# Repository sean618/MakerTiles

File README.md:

# MakerTiles

MakerTiles is a system of modular, snap-together electronic tiles. Each tile is a
small STM32-based board with a single job — a strip of LEDs, a joystick, a motor,
a distance sensor, a screen, a speaker, and so on. Tiles connect on a shared bus,
a USB tile bridges the bus to a PC, and a Python daemon on the PC discovers every
connected tile and lets you read its inputs and drive its outputs.

This repository holds the whole stack: the **hardware** (KiCad board designs), the
**firmware** (STM32 board projects + shared driver libraries), the **protocols**
that move data over the bus, and the **daemon** that talks to it all from a PC.

```
    [ tile ]──[ tile ]──[ tile ]── … ──[ USB tile ]──USB──▶ [ PC / Python daemon ]
       └───────────────────────────────────┘
          shared SPI bus  (MicroBus + Field Protocol)
```

## How it fits together

Two protocols stacked on top of each other carry everything:

- **MicroBus** — the transport. A master/multi-node protocol over a shared
  SPI-style link between microcontrollers, built for speed and very low RAM:
  fixed-size packets, a time-slotted schedule the master broadcasts in every
  packet, and a small per-node sliding window that gives reliable, in-order
  delivery with no dynamic allocation.
- **Field Protocol** — the application layer. Rides inside a MicroBus packet and
  describes each tile as a set of named, typed **fields** (e.g. a LED strip's
  colour, a dial's position). The daemon enumerates tiles, reads their field
  tables, and gets/sets field values without knowing the tile type in advance.

One tile acts as the **master** (the USB tile, which also bridges the bus to a
host PC). Every other tile is a **node**. On the PC, the daemon opens the USB
serial port, discovers the attached tiles, and exposes each one as an object you
can interact with.

## Repository layout

```
hardware/        KiCad designs for every tile (Boards/) + shared symbol/footprint
                 libraries, 3D models and BOMs (Libraries/). Old/ holds retired
                 prototype boards.

firmware/        STM32 firmware.
  Boards/          One STM32CubeIDE project per tile (Button, LedStrip, Motor,
                   Joystick, Screen, USB, …). Mostly STM32G030 nodes; the USB
                   master is an STM32F103.
  Libraries/       Shared C/C++ drivers used across boards (ledStrip, screen,
                   imu, speaker, servos, …) plus helpers (myAssert, fonts).
  Documents/       NewBoardSetup.txt — the checklist for bringing up a new tile
                   (CubeMX peripheral config + firmware wiring).

protocol/        The shared protocol code, host-buildable and testable.
  microbus/        MicroBus transport (C++). Leaf component.
  fieldprotocol/   Field Protocol (C++), depends on microbus. Also built as the
                   masterNodeSystem shared library the Python daemon loads.
  stm32/           STM32 glue binding the protocols to real SPI hardware
                   (stm32F1SpiMaster, stm32Node). Boards reach this via a
                   Core/stm32 symlink.

daemon/          Python daemon (the PC side). Opens the USB serial port, runs
                   board discovery, and drives tiles over the Field Protocol.
                   src/makertiles/ is the package; tests/ holds its test suites.

tests/system/    Full C stack (node + master) over the real MicroBus, in-process.

tools/           Helper scripts (e.g. logparser.py).
```

## The PC daemon

The daemon is a Python package (`makertiles`, src-layout under `daemon/`). At a
high level you point it at a serial port and it hands you back the discovered
tiles:

```python
import makertiles

tiles, manager = makertiles.start(port_name="/dev/ttyUSB0")

tiles.led_strip.colour = makertiles.red   # set an output field
position = tiles.dial.position             # read an input field
```

It can drive the C protocol two ways: over **serial** to real hardware in
production, or — in tests — by loading the `masterNodeSystem` shared library
directly via `ctypes`, so the real Python daemon exercises the real C protocol
without any hardware attached. That same library is what catches drift between
the C and Python sides of the wire contract.

Optional extras: `Pillow` (`images`) for the screen image-drawing helpers.

## Building and testing

The C components and the Python daemon build in one CMake tree, and every test
suite runs from a single command:

```bash
./build_and_test.sh
```

This configures, builds (MicroBus, the Field Protocol + its shared library, and
the system test), then runs `ctest`. Python test deps (`pytest`, `pyserial`) are
installed automatically if missing.

To re-run only the failures, verbosely:

```bash
ctest --test-dir build --rerun-failed --output-on-failure
```

### Test suites

| CTest name           | What it covers                                              |
|----------------------|-------------------------------------------------------------|
| `microbus_unit`      | MicroBus transport unit tests (host).                       |
| `fieldprotocol_unit` | Field Protocol unit tests against a mock MicroBus.          |
| `system_integration` | Full C stack (node + master) over the real MicroBus.        |
| `python_unit`        | Python Field-Protocol encode/decode round trips.            |
| `python_integration` | The real Python daemon driving the C protocol via the .so.  |

`python_integration` is the suite that exercises both languages together, so it
is the one that catches C↔Python wire-contract drift.

The firmware board projects under `firmware/Boards/` are separate
STM32CubeIDE/CMake projects and are **not** part of the host build above — they
are flashed to real tiles. See `firmware/Documents/NewBoardSetup.txt` for the
per-board hardware and firmware bring-up checklist.

## Building firmware for a tile

Each `firmware/Boards/<Tile>/` directory is its own STM32 project (`.ioc` for
CubeMX, a linker script for the target part, and CubeIDE debug launch configs).
Nodes are generally STM32G030; the USB master is an STM32F103. The protocol
sources are shared into each board via symlinks (`Core/stm32`,
`Core/Libraries`, etc.) rather than copied — see the setup checklist for the
exact links and the required SPI/timer/interrupt peripheral configuration.

## License

Released under the [MIT License](LICENSE).

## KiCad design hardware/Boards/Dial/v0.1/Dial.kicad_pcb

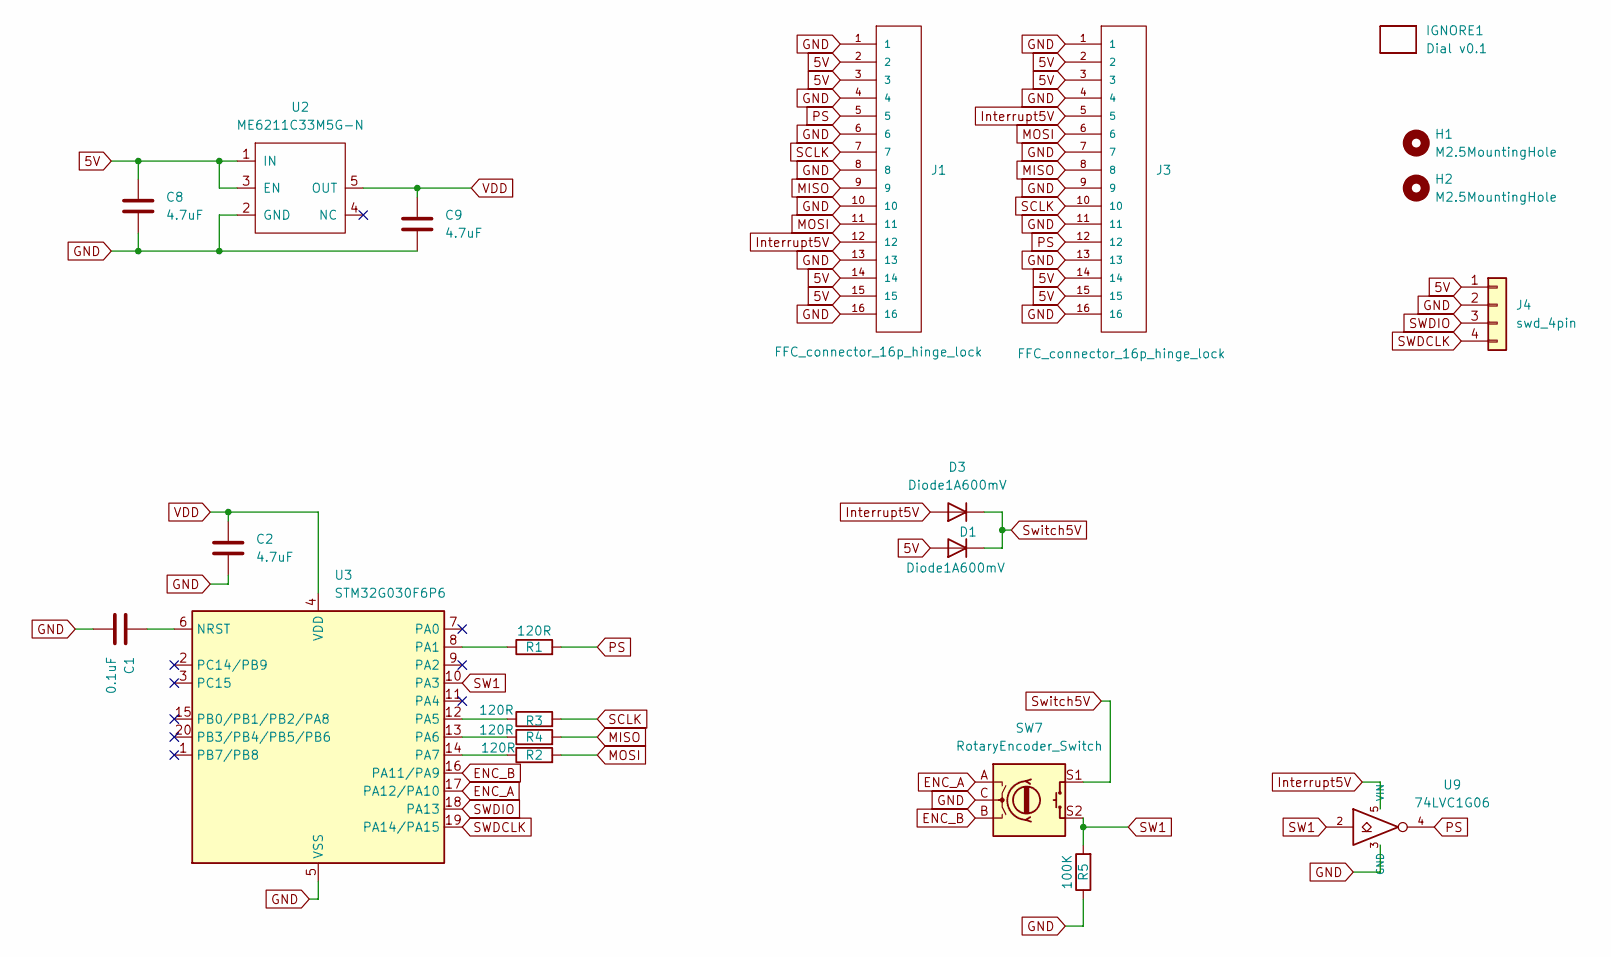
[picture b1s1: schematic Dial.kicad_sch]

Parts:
C1: 0.1uF; C_0402_1005Metric
C2, C8, C9: 4.7uF; C_0402_1005Metric
D1, D3: Diode1A600mV; D_SOD-323
H1, H2: M2.5MountingHole; MountingHole_2.7mm_M2.5_ISO7380
IGNORE1: Dial v0.1; BoardText
J1, J3: FFC_connector_16p_hinge_lock
J4: swd_4pin; swd_header
R1, R2, R3, R4: 120R; R_0402_1005Metric
R5: 100K; R_0402_1005Metric
SW7: RotaryEncoder_Switch; RotaryEncoderEC12D
U2: ME6211C33M5G-N; SOT-23-5
U3: STM32G030F6P6; TSSOP-20_4.4x6.5mm_P0.65mm
U9: 74LVC1G06; SOT-353_SC-70-5

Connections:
5V: C8.1, D1.2 (A), J1.2, J1.3, J1.14, J1.15, J3.2, J3.3, J3.14, J3.15, J4.1, U2.1 (IN), U2.3 (EN)
ENC_A: SW7.A, U3.17 (PA12/PA10)
ENC_B: SW7.B, U3.16 (PA11/PA9)
GND: C1.2, C2.2, C8.2, C9.2, J1.1, J1.4, J1.6, J1.8, J1.10, J1.13, J1.16, J3.1, J3.4, J3.7, J3.9, J3.11, J3.13, J3.16, J4.2, R5.1, SW7.C, U2.2 (GND), U3.5 (VSS), U9.3 (GND)
Interrupt5V: D3.2 (A), J1.12, J3.5, U9.5 (VIN)
MISO: J1.9, J3.8, R4.2
MOSI: J1.11, J3.6, R2.2
unnamed: C1.1, U3.6 (NRST)
unnamed: R1.1, U3.8 (PA1)
unnamed: R3.1, U3.12 (PA5)
unnamed: R4.1, U3.13 (PA6)
unnamed: R2.1, U3.14 (PA7)
PS: J1.5, J3.12, R1.2, U9.4
SCLK: J1.7, J3.10, R3.2
SW1: R5.2, SW7.S2, U3.10 (PA3), U9.2
SWDCLK: J4.4, U3.19 (PA14/PA15)
SWDIO: J4.3, U3.18 (PA13)
Switch5V: D1.1 (K), D3.1 (K), SW7.S1
VDD: C2.1, C9.1, U2.5 (OUT), U3.4 (VDD)

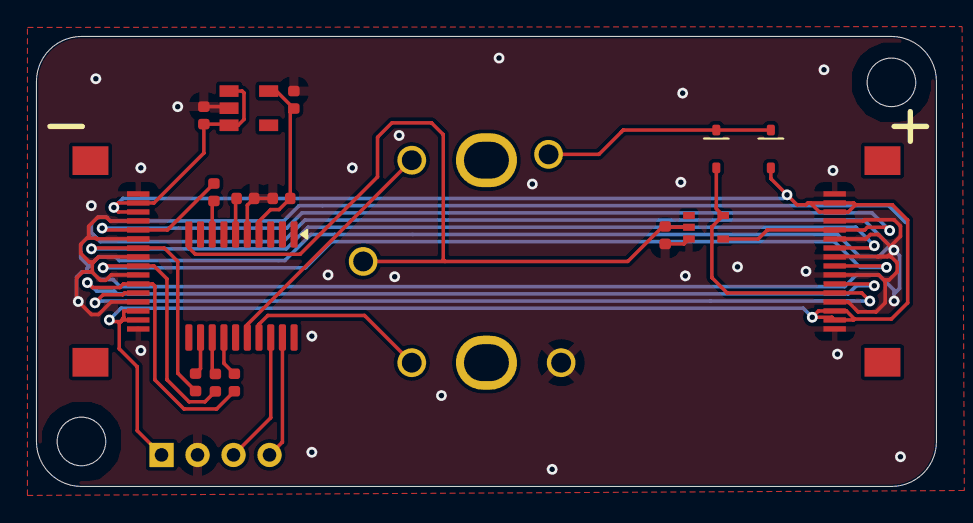
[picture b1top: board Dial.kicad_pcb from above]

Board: 2 copper layers, 50.0 x 25.0 mm, 21 parts (0 on the bottom side), 19 nets.

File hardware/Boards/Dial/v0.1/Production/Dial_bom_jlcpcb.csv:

Comment,Designator,Footprint,LCSC Part Number
4.7uF,"C9,C8,C2",C_0402_1005Metric,C23733
FFC_connector_16p_hinge_lock,"J1,J3",FFC_connector_16p_hinge_lock,C262665
Diode1A600mV,"D3,D1",D_SOD-323,C191023
74LVC1G06,U9,SOT-353_SC-70-5,C460519
ME6211C33M5G-N,U2,SOT-23-5,C81233
120R,"R2,R4,R1,R3",R_0402_1005Metric,C25079
RotaryEncoder_Switch,SW7,RotaryEncoderEC12D,C112349
STM32G030F6P6,U3,TSSOP-20_4.4x6.5mm_P0.65mm,C529330
100K,R5,R_0402_1005Metric,C25741
0.1uF,C1,C_0402_1005Metric,C1525

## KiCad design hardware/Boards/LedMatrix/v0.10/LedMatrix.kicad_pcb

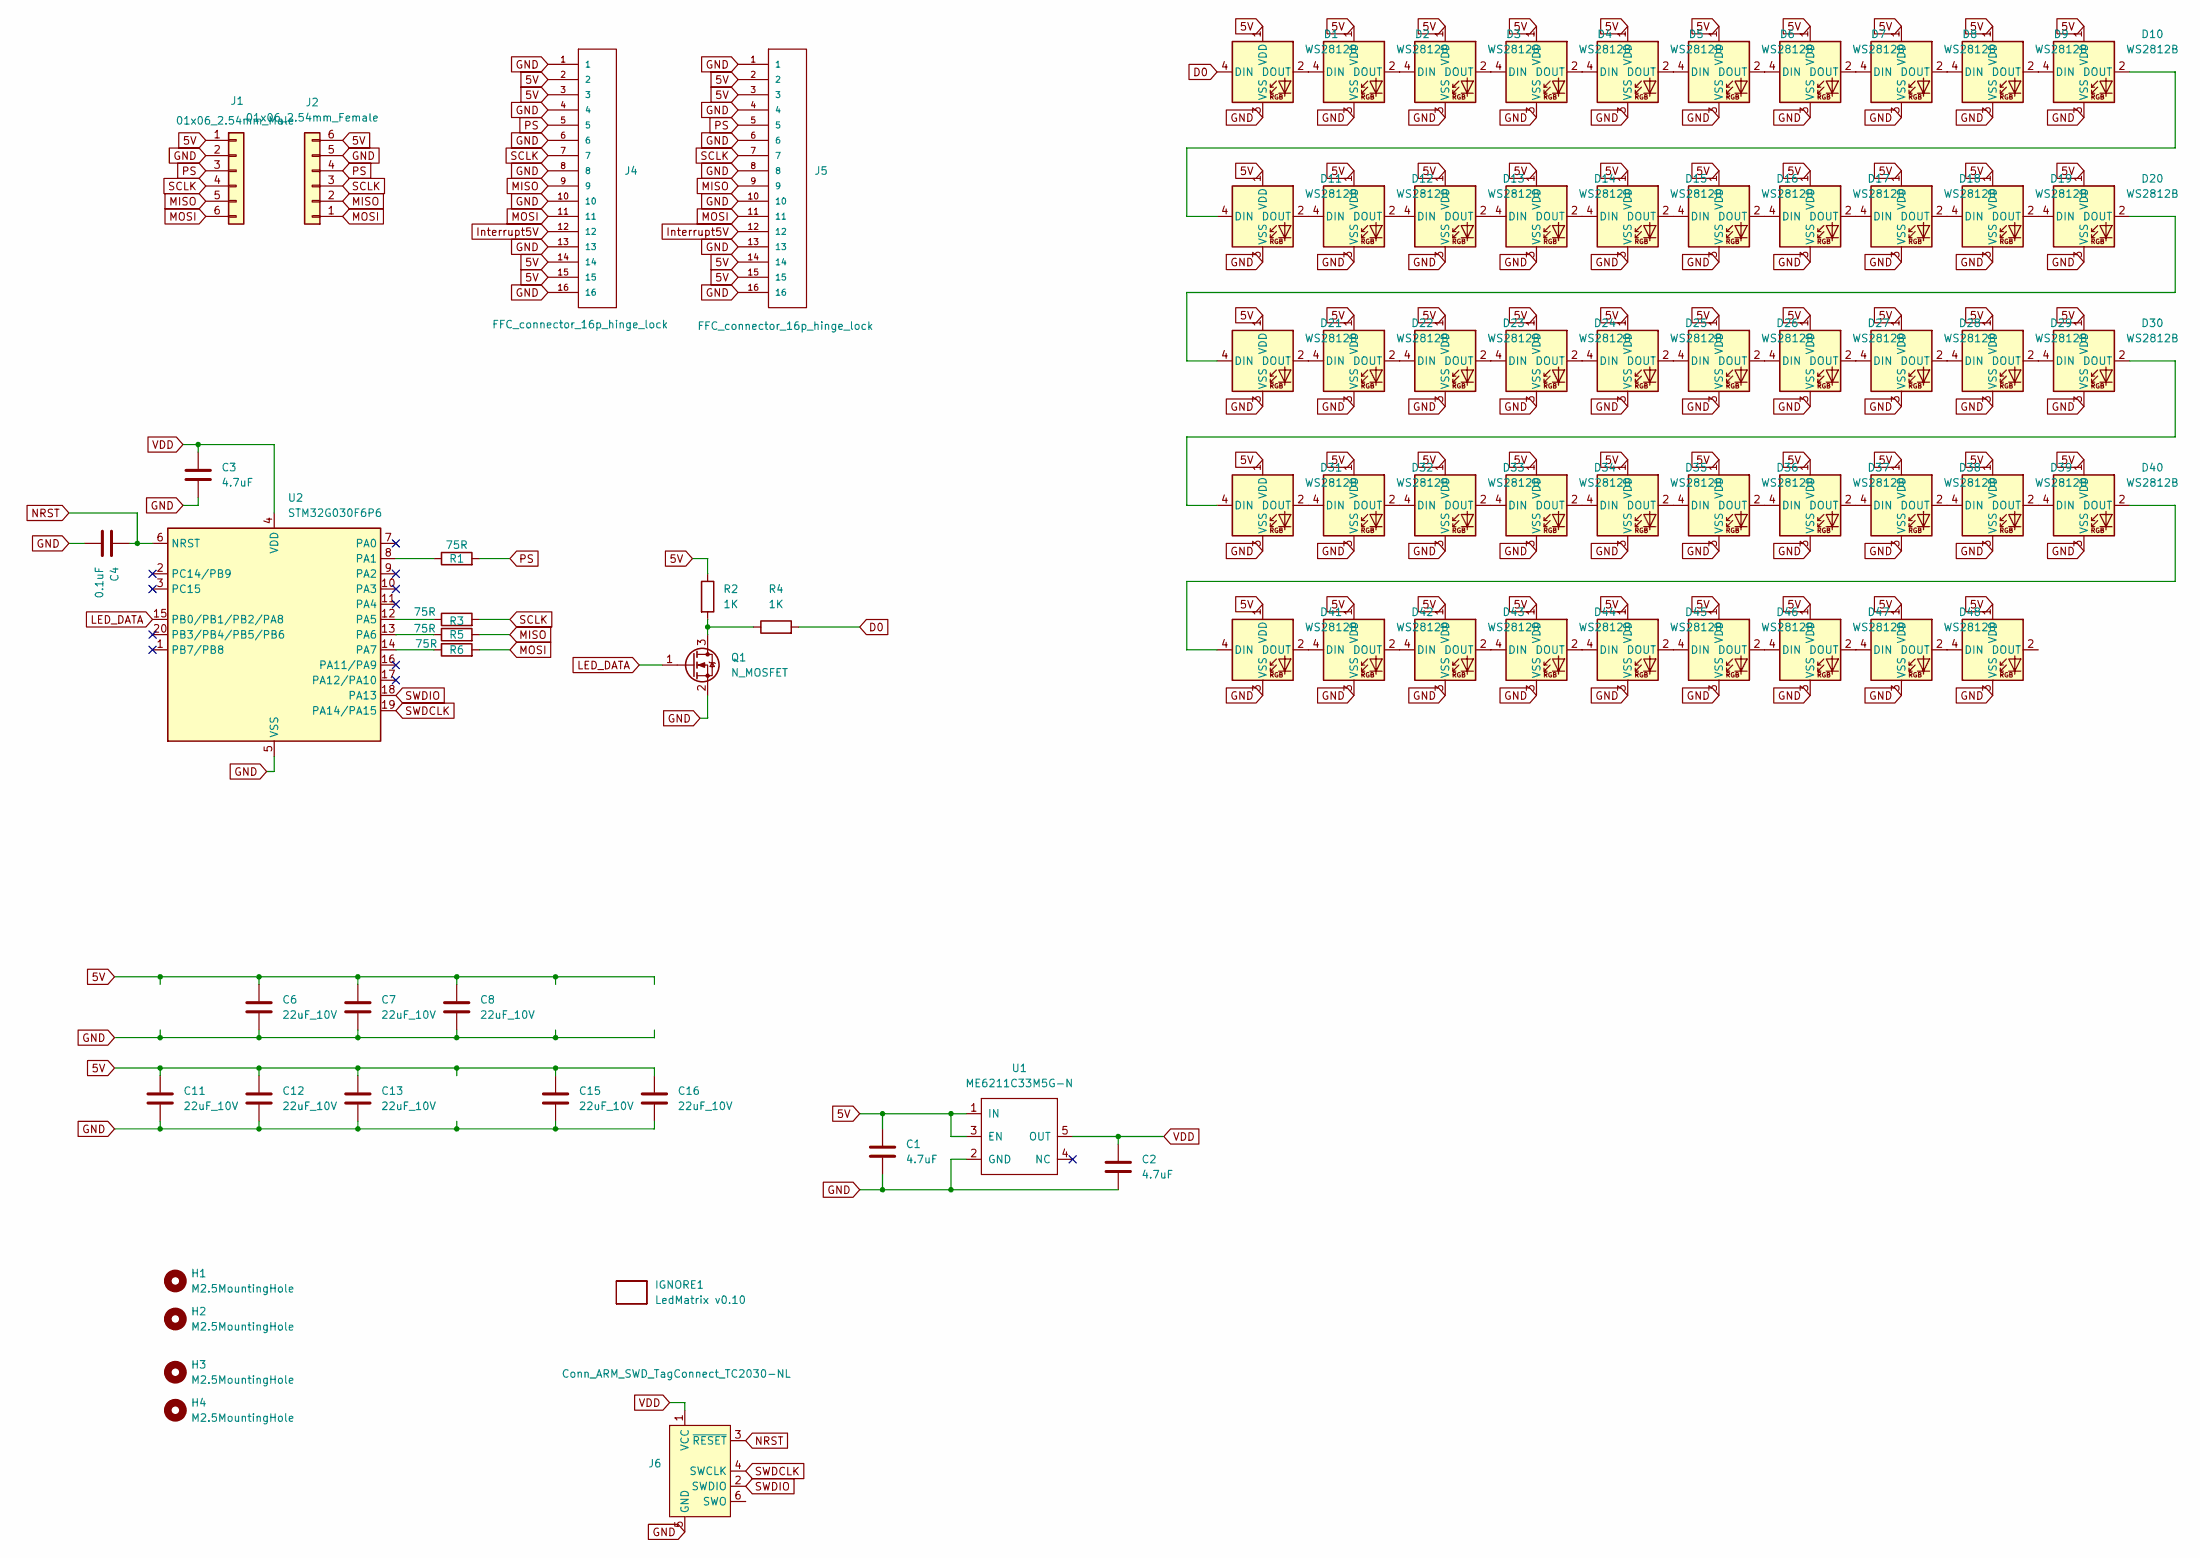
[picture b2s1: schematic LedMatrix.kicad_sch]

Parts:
C1, C2, C3: 4.7uF; C_0402_1005Metric
C4: 0.1uF; C_0402_1005Metric
C6, C7, C8, C11, C12, C13, C15, C16: 22uF_10V; C_0603_1608Metric
D1, D2, D3, D4, D5, D6, D7, D8, D9, D10, D11, D12, D13, D14, D15, D16, D17, D18, D19, D20, D21, D22, D23, D24, D25, D26, D27, D28, D29, D30, D31, D32, D33, D34, D35, D36, D37, D38, D39, D40, D41, D42, D43, D44, D45, D46, D47, D48, D49: WS2812B; LED_WS2812B_PLCC4_5.0x5.0mm_P3.2mm
H1, H2, H3, H4: M2.5MountingHole; MountingHole_2.7mm_M2.5_ISO7380
IGNORE1: LedMatrix v0.10; BoardText
J1: 01x06_2.54mm_Male
J2: 01x06_2.54mm_Female
J4, J5: FFC_connector_16p_hinge_lock
J6: Conn_ARM_SWD_TagConnect_TC2030-NL; Tag-Connect_TC2030-IDC-NL_2x03_P1.27mm_Vertical
Q1: N_MOSFET; SOT-23
R1, R3, R5, R6: 75R; R_0402_1005Metric
R2, R4: 1K; R_0402_1005Metric
U1: ME6211C33M5G-N; SOT-23-5
U2: STM32G030F6P6; TSSOP-20_4.4x6.5mm_P0.65mm

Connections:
5V: C1.1, C6.1, C7.1, C8.1, C11.1, C12.1, C13.1, C15.1, C16.1, D1.1 (VDD), D2.1 (VDD), D3.1 (VDD), D4.1 (VDD), D5.1 (VDD), D6.1 (VDD), D7.1 (VDD), D8.1 (VDD), D9.1 (VDD), D10.1 (VDD), D11.1 (VDD), D12.1 (VDD), D13.1 (VDD), D14.1 (VDD), D15.1 (VDD), D16.1 (VDD), D17.1 (VDD), D18.1 (VDD), D19.1 (VDD), D20.1 (VDD), D21.1 (VDD), D22.1 (VDD), D23.1 (VDD), D24.1 (VDD), D25.1 (VDD), D26.1 (VDD), D27.1 (VDD), D28.1 (VDD), D29.1 (VDD), D30.1 (VDD), D31.1 (VDD), D32.1 (VDD), D33.1 (VDD), D34.1 (VDD), D35.1 (VDD), D36.1 (VDD), D37.1 (VDD), D38.1 (VDD), D39.1 (VDD), D40.1 (VDD), D41.1 (VDD), D42.1 (VDD), D43.1 (VDD), D44.1 (VDD), D45.1 (VDD), D46.1 (VDD), D47.1 (VDD), D48.1 (VDD), D49.1 (VDD), J1.1, J2.6, J4.2, J4.3, J4.14, J4.15, J5.2, J5.3, J5.14, J5.15, R2.1, U1.1 (IN), U1.3 (EN)
D0: D1.4 (DIN), R4.2
GND: C1.2, C2.2, C3.2, C4.2, C6.2, C7.2, C8.2, C11.2, C12.2, C13.2, C15.2, C16.2, D1.3 (VSS), D2.3 (VSS), D3.3 (VSS), D4.3 (VSS), D5.3 (VSS), D6.3 (VSS), D7.3 (VSS), D8.3 (VSS), D9.3 (VSS), D10.3 (VSS), D11.3 (VSS), D12.3 (VSS), D13.3 (VSS), D14.3 (VSS), D15.3 (VSS), D16.3 (VSS), D17.3 (VSS), D18.3 (VSS), D19.3 (VSS), D20.3 (VSS), D21.3 (VSS), D22.3 (VSS), D23.3 (VSS), D24.3 (VSS), D25.3 (VSS), D26.3 (VSS), D27.3 (VSS), D28.3 (VSS), D29.3 (VSS), D30.3 (VSS), D31.3 (VSS), D32.3 (VSS), D33.3 (VSS), D34.3 (VSS), D35.3 (VSS), D36.3 (VSS), D37.3 (VSS), D38.3 (VSS), D39.3 (VSS), D40.3 (VSS), D41.3 (VSS), D42.3 (VSS), D43.3 (VSS), D44.3 (VSS), D45.3 (VSS), D46.3 (VSS), D47.3 (VSS), D48.3 (VSS), D49.3 (VSS), J1.2, J2.5, J4.1, J4.4, J4.6, J4.8, J4.10, J4.13, J4.16, J5.1, J5.4, J5.6, J5.8, J5.10, J5.13, J5.16, J6.5 (GND), Q1.2 (S), U1.2 (GND), U2.5 (VSS)
Interrupt5V: J4.12, J5.12
LED_DATA: Q1.1 (G), U2.15 (PB0/PB1/PB2/PA8)
MISO: J1.5, J2.2, J4.9, J5.9, R5.2
MOSI: J1.6, J2.1, J4.11, J5.11, R6.2
NRST: C4.1, J6.3 (~RESET), U2.6 (NRST)
unnamed: D1.2 (DOUT), D2.4 (DIN)
unnamed: D2.2 (DOUT), D3.4 (DIN)
unnamed: D3.2 (DOUT), D4.4 (DIN)
unnamed: D4.2 (DOUT), D5.4 (DIN)
unnamed: D5.2 (DOUT), D6.4 (DIN)
unnamed: D6.2 (DOUT), D7.4 (DIN)
unnamed: D7.2 (DOUT), D8.4 (DIN)
unnamed: D8.2 (DOUT), D9.4 (DIN)
unnamed: D9.2 (DOUT), D10.4 (DIN)
unnamed: D10.2 (DOUT), D11.4 (DIN)
unnamed: D11.2 (DOUT), D12.4 (DIN)
unnamed: D12.2 (DOUT), D13.4 (DIN)
unnamed: D13.2 (DOUT), D14.4 (DIN)
unnamed: D14.2 (DOUT), D15.4 (DIN)
unnamed: D15.2 (DOUT), D16.4 (DIN)
unnamed: D16.2 (DOUT), D17.4 (DIN)
unnamed: D17.2 (DOUT), D18.4 (DIN)
unnamed: D18.2 (DOUT), D19.4 (DIN)
unnamed: D19.2 (DOUT), D20.4 (DIN)
unnamed: D20.2 (DOUT), D21.4 (DIN)
unnamed: D21.2 (DOUT), D22.4 (DIN)
unnamed: D22.2 (DOUT), D23.4 (DIN)
unnamed: D23.2 (DOUT), D24.4 (DIN)
unnamed: D24.2 (DOUT), D25.4 (DIN)
unnamed: D25.2 (DOUT), D26.4 (DIN)
unnamed: D26.2 (DOUT), D27.4 (DIN)
unnamed: D27.2 (DOUT), D28.4 (DIN)
unnamed: D28.2 (DOUT), D29.4 (DIN)
unnamed: D29.2 (DOUT), D30.4 (DIN)
unnamed: D30.2 (DOUT), D31.4 (DIN)
unnamed: D31.2 (DOUT), D32.4 (DIN)
unnamed: D32.2 (DOUT), D33.4 (DIN)
unnamed: D33.2 (DOUT), D34.4 (DIN)
unnamed: D34.2 (DOUT), D35.4 (DIN)
unnamed: D35.2 (DOUT), D36.4 (DIN)
unnamed: D36.2 (DOUT), D37.4 (DIN)
unnamed: D37.2 (DOUT), D38.4 (DIN)
unnamed: D38.2 (DOUT), D39.4 (DIN)
unnamed: D39.2 (DOUT), D40.4 (DIN)
unnamed: D40.2 (DOUT), D41.4 (DIN)
unnamed: D41.2 (DOUT), D42.4 (DIN)
unnamed: D42.2 (DOUT), D43.4 (DIN)
unnamed: D43.2 (DOUT), D44.4 (DIN)
unnamed: D44.2 (DOUT), D45.4 (DIN)
unnamed: D45.2 (DOUT), D46.4 (DIN)
unnamed: D46.2 (DOUT), D47.4 (DIN)
unnamed: D47.2 (DOUT), D48.4 (DIN)
unnamed: D48.2 (DOUT), D49.4 (DIN)
unnamed: Q1.3 (D), R2.2, R4.1
unnamed: R1.1, U2.8 (PA1)
unnamed: R3.1, U2.12 (PA5)
unnamed: R5.1, U2.13 (PA6)
unnamed: R6.1, U2.14 (PA7)
PS: J1.3, J2.4, J4.5, J5.5, R1.2
SCLK: J1.4, J2.3, J4.7, J5.7, R3.2
SWDCLK: J6.4 (SWCLK), U2.19 (PA14/PA15)
SWDIO: J6.2 (SWDIO), U2.18 (PA13)
VDD: C2.1, C3.1, J6.1 (VCC), U1.5 (OUT), U2.4 (VDD)

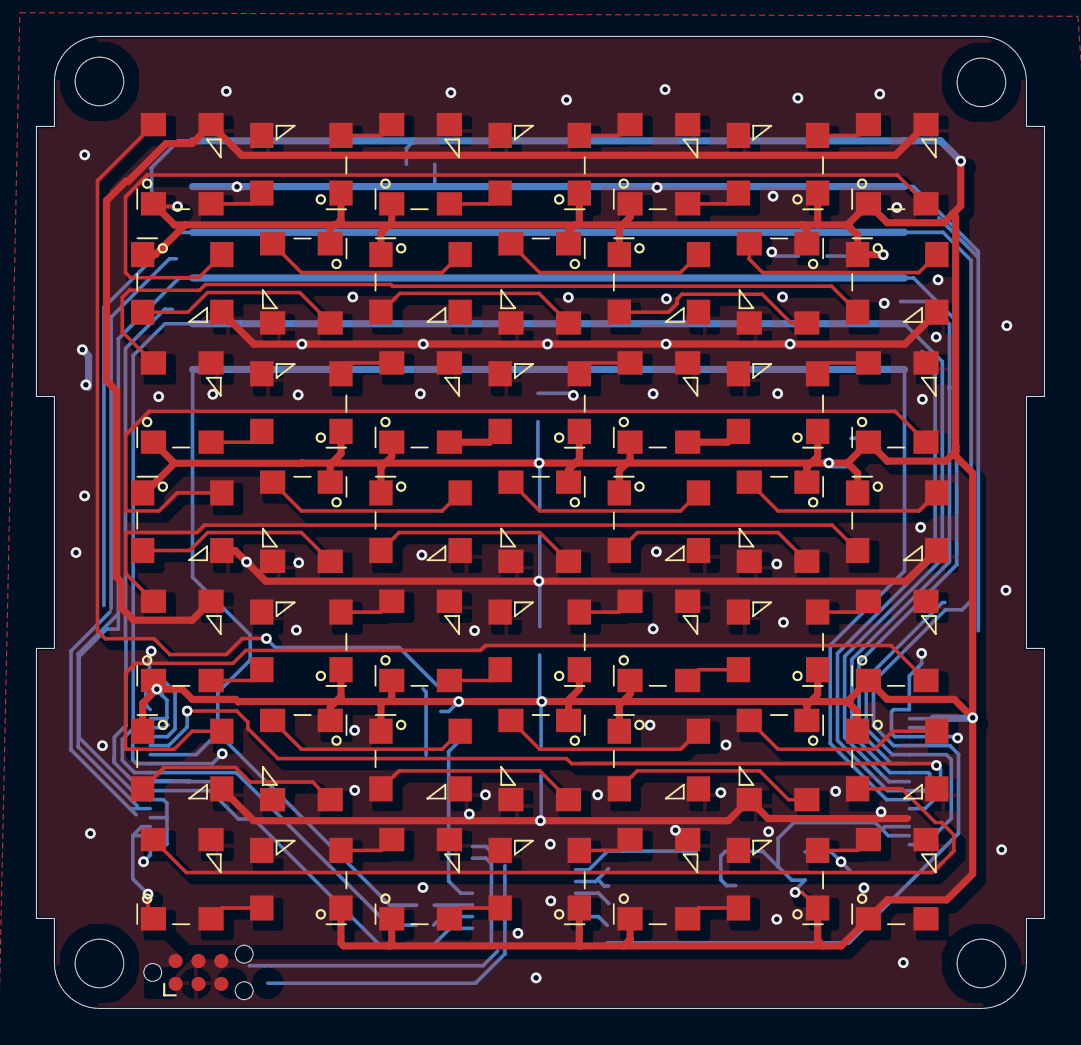
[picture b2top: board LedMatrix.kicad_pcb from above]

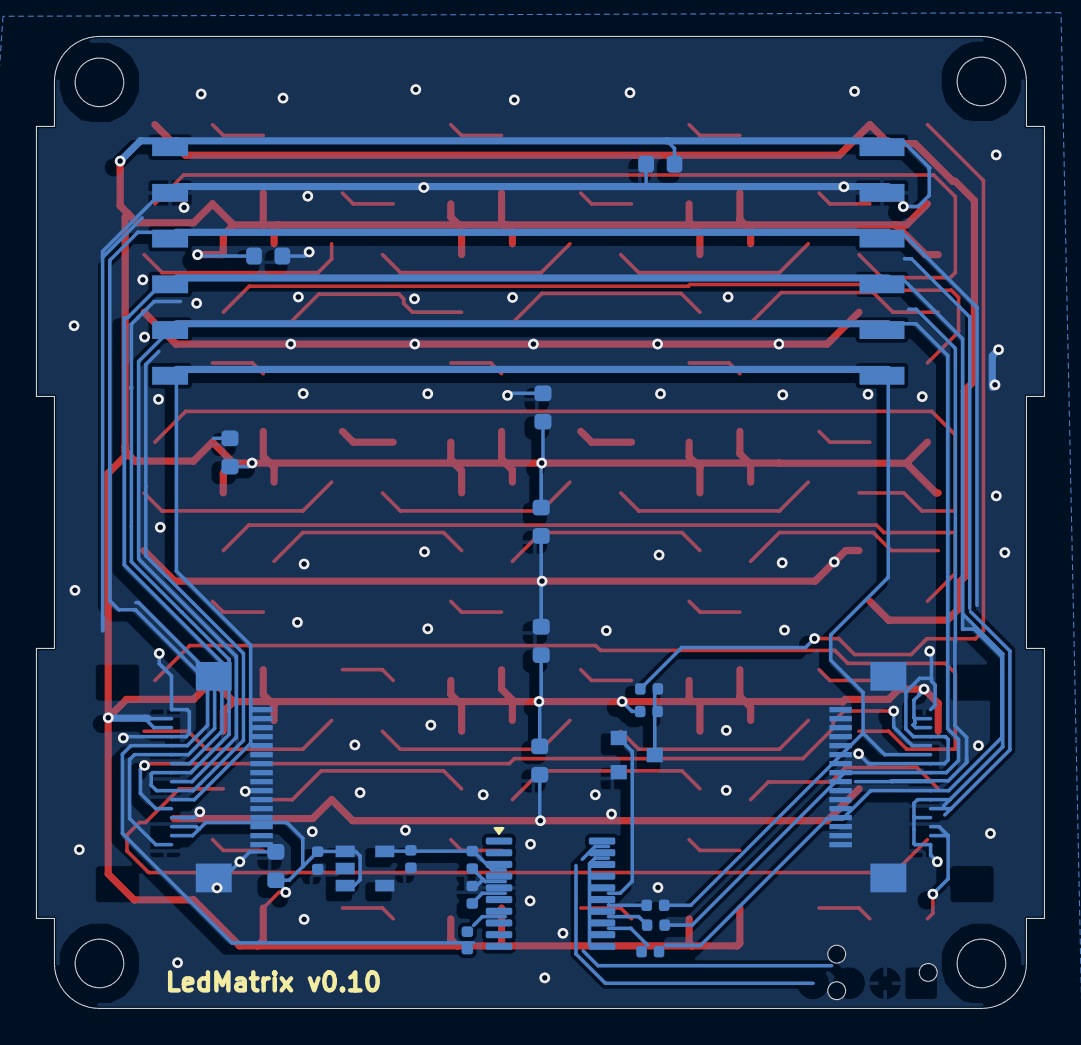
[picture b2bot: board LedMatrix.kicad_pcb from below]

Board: 4 copper layers, 56.0 x 54.0 mm, 80 parts (25 on the bottom side), 66 nets.

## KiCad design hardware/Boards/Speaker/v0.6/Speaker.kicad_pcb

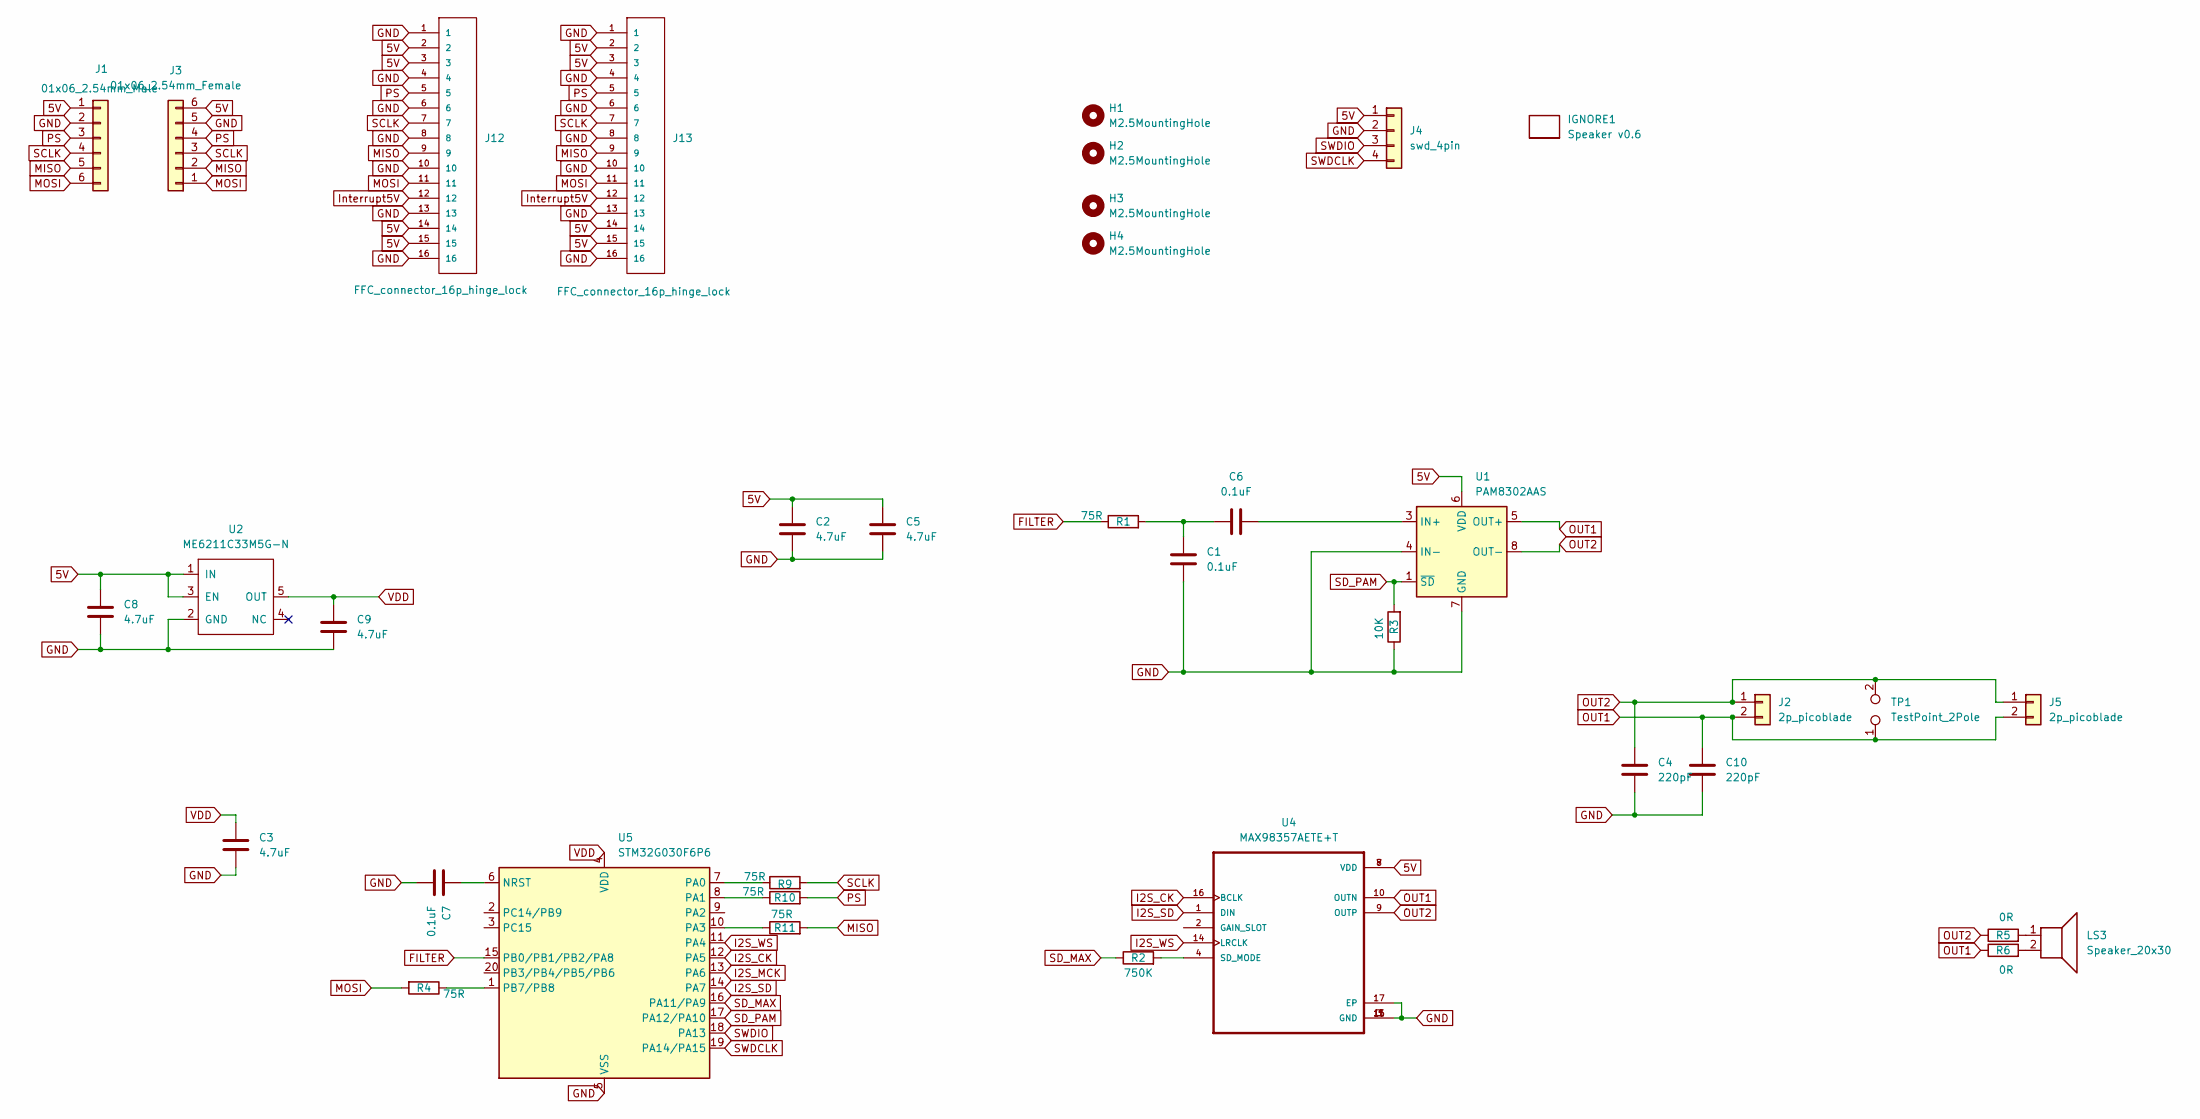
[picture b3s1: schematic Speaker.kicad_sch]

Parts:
C1, C6, C7: 0.1uF; C_0402_1005Metric
C2, C3, C5, C8, C9: 4.7uF; C_0402_1005Metric
C4, C10: 220pF; C_0402_1005Metric
H1, H2, H3, H4: M2.5MountingHole; MountingHole_2.7mm_M2.5_ISO7380
IGNORE1: Speaker v0.6; BoardText
J1: 01x06_2.54mm_Male
J2, J5: 2p_picoblade; Molex_PicoBlade_53261-0271_1x02-1MP_P1.25mm_Horizontal
J3: 01x06_2.54mm_Female
J4: swd_4pin; swd_header
J12, J13: FFC_connector_16p_hinge_lock
LS3: Speaker_20x30; Speaker1.8x1.8
R1, R4, R9, R10, R11: 75R; R_0402_1005Metric
R2: 750K; R_0402_1005Metric
R3: 10K; R_0402_1005Metric
R5, R6: 0R; R_0402_1005Metric
TP1: TestPoint_2Pole; TestPoint_2Pads_Pitch2.54mm_Drill0.8mm
U1: PAM8302AAS; MSOP-8_3x3mm_P0.65mm
U2: ME6211C33M5G-N; SOT-23-5
U4: MAX98357AETE+T; QFN50P300X300X80-17N
U5: STM32G030F6P6; TSSOP-20_4.4x6.5mm_P0.65mm

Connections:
5V: C2.1, C5.1, C8.1, J1.1, J3.6, J4.1, J12.2, J12.3, J12.14, J12.15, J13.2, J13.3, J13.14, J13.15, U1.6 (VDD), U2.1 (IN), U2.3 (EN), U4.7 (VDD), U4.8 (VDD)
FILTER: R1.1, U5.15 (PB0/PB1/PB2/PA8)
GND: C1.2, C2.2, C3.2, C4.2, C5.2, C7.2, C8.2, C9.2, C10.2, J1.2, J3.5, J4.2, J12.1, J12.4, J12.6, J12.8, J12.10, J12.13, J12.16, J13.1, J13.4, J13.6, J13.8, J13.10, J13.13, J13.16, R3.1, U1.4 (IN-), U1.7 (GND), U2.2 (GND), U4.3 (GND), U4.11 (GND), U4.15 (GND), U4.17 (EP), U5.5 (VSS)
I2S_CK: U4.16 (BCLK), U5.12 (PA5)
I2S_MCK: U5.13 (PA6)
I2S_SD: U4.1 (DIN), U5.14 (PA7)
I2S_WS: U4.14 (LRCLK), U5.11 (PA4)
Interrupt5V: J12.12, J13.12
MISO: J1.5, J3.2, J12.9, J13.9, R11.2
MOSI: J1.6, J3.1, J12.11, J13.11, R4.2
unnamed: C1.1, C6.2, R1.2
unnamed: LS3.1, R5.2
unnamed: LS3.2, R6.2
unnamed: C6.1, U1.3 (IN+)
unnamed: R2.2, U4.4 (SD_MODE)
unnamed: C7.1, U5.6 (NRST)
unnamed: R9.1, U5.7 (PA0)
unnamed: R10.1, U5.8 (PA1)
unnamed: R11.1, U5.10 (PA3)
unnamed: R4.1, U5.1 (PB7/PB8)
OUT1: C10.1, J2.2, J5.2, R6.1, TP1.1, U1.5 (OUT+), U4.10 (OUTN)
OUT2: C4.1, J2.1, J5.1, R5.1, TP1.2, U1.8 (OUT-), U4.9 (OUTP)
PS: J1.3, J3.4, J12.5, J13.5, R10.2
SCLK: J1.4, J3.3, J12.7, J13.7, R9.2
SD_MAX: R2.1, U5.16 (PA11/PA9)
SD_PAM: R3.2, U1.1 (~SD), U5.17 (PA12/PA10)
SWDCLK: J4.4, U5.19 (PA14/PA15)
SWDIO: J4.3, U5.18 (PA13)
VDD: C3.1, C9.1, U2.5 (OUT), U5.4 (VDD)

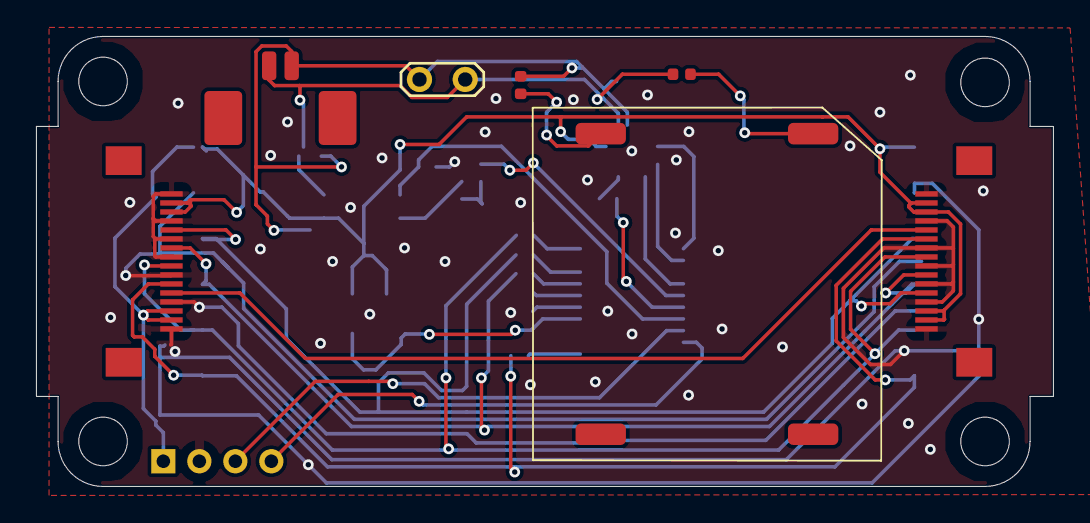
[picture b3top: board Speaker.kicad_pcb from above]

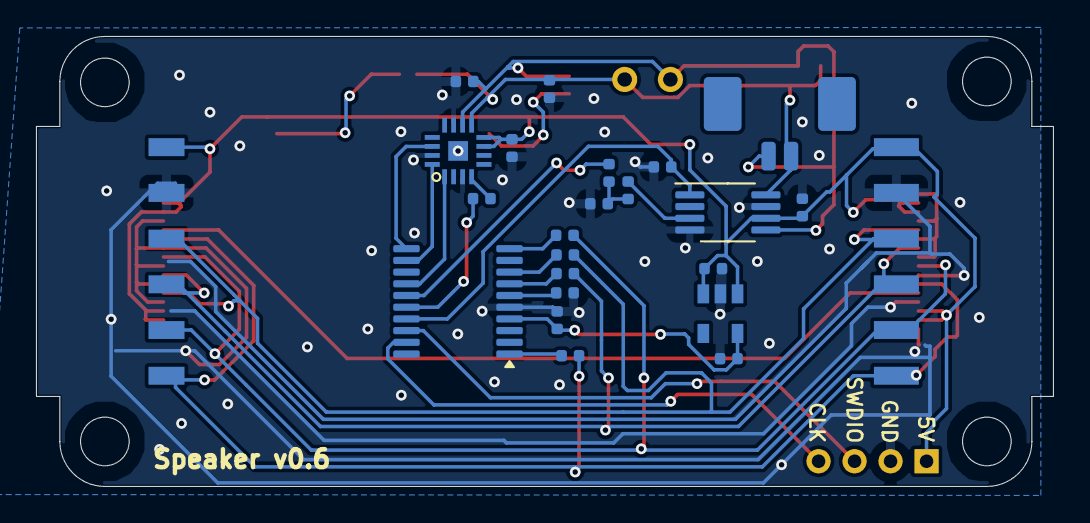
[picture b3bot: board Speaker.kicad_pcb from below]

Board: 2 copper layers, 56.5 x 25.0 mm, 37 parts (24 on the bottom side), 28 nets.

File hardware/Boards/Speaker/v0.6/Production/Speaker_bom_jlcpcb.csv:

Comment,Designator,Footprint,LCSC Part Number
FFC_connector_16p_hinge_lock,"J12,J13,J6",FFC_connector_16p_hinge_lock,C262665
2p_picoblade,"J2,J5",Molex_PicoBlade_53261-0271_1x02-1MP_P1.25mm_Horizontal,C189700
4.7uF,"C9,C5,C3,C8,C2",C_0402_1005Metric,C23733
220pF,"C10,C4",C_0402_1005Metric,C1530
75R,"R4,R9,R10,R1,R11",R_0402_1005Metric,C25133
01x06_2.54mm_Male,J1,01x06_2.54mm_Male,C5242199
01x06_2.54mm_Female,J3,01x06_2.54mm_Female,C5142239
0.1uF,"C1,C7,C6",C_0402_1005Metric,C1525
STM32G030F6P6,U5,TSSOP-20_4.4x6.5mm_P0.65mm,C529330
ME6211C33M5G-N,U2,SOT-23-5,C81233
750K,R2,R_0402_1005Metric,C43291
MAX98357AETE+T,U4,QFN50P300X300X80-17N,C910544
Speaker_20x30,LS1,Speaker_20x30,C28642278
10K,R3,R_0402_1005Metric,C25744
PAM8302AAS,U1,MSOP-8_3x3mm_P0.65mm,C113367

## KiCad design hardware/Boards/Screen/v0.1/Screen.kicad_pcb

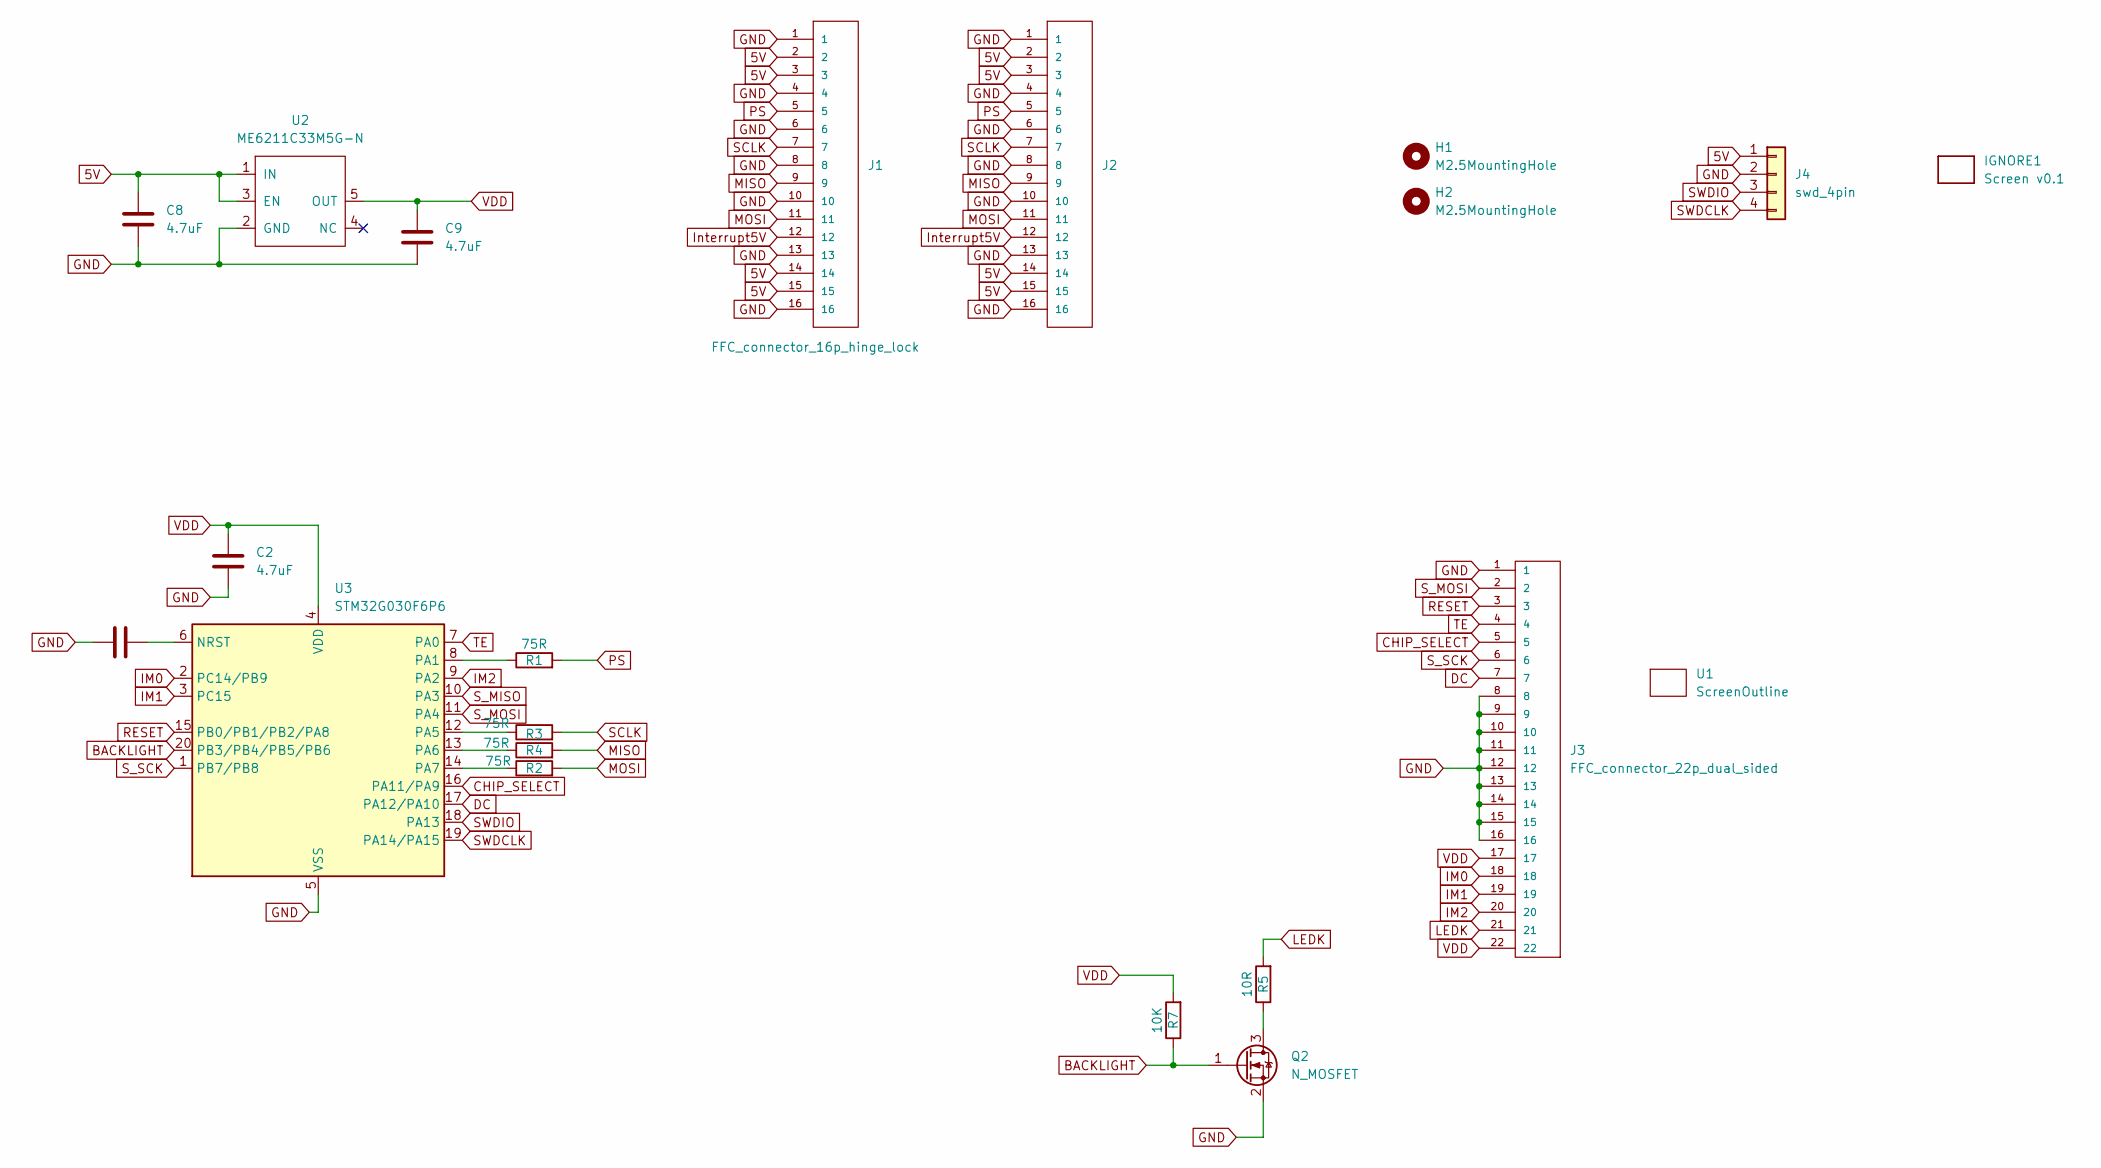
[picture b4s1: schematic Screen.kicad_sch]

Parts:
C1: 0.1uF; C_0402_1005Metric
C2, C8, C9: 4.7uF; C_0402_1005Metric
H1, H2: M2.5MountingHole; MountingHole_2.7mm_M2.5_ISO7380
IGNORE1: Screen v0.1; BoardText
J1, J2: FFC_connector_16p_hinge_lock
J3: FFC_connector_22p_dual_sided; FFC_connector_22p_hinge_lock
J4: swd_4pin; swd_header
Q2: N_MOSFET; SOT-23
R1, R2, R3, R4: 75R; R_0402_1005Metric
R5: 10R; R_0402_1005Metric
R7: 10K; R_0402_1005Metric
U1: ScreenOutline; 2InchScreen
U2: ME6211C33M5G-N; SOT-23-5
U3: STM32G030F6P6; TSSOP-20_4.4x6.5mm_P0.65mm

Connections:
5V: C8.1, J1.2, J1.3, J1.14, J1.15, J2.2, J2.3, J2.14, J2.15, J4.1, U2.1 (IN), U2.3 (EN)
BACKLIGHT: Q2.1 (G), R7.1, U3.20 (PB3/PB4/PB5/PB6)
CHIP_SELECT: J3.5, U3.16 (PA11/PA9)
DC: J3.7, U3.17 (PA12/PA10)
GND: C1.2, C2.2, C8.2, C9.2, J1.1, J1.4, J1.6, J1.8, J1.10, J1.13, J1.16, J2.1, J2.4, J2.6, J2.8, J2.10, J2.13, J2.16, J3.1, J3.8, J3.9, J3.10, J3.11, J3.12, J3.13, J3.14, J3.15, J3.16, J4.2, Q2.2 (S), U2.2 (GND), U3.5 (VSS)
IM0: J3.18, U3.2 (PC14/PB9)
IM1: J3.19, U3.3 (PC15)
IM2: J3.20, U3.9 (PA2)
Interrupt5V: J1.12, J2.12
LEDK: J3.21, R5.2
MISO: J1.9, J2.9, R4.2
MOSI: J1.11, J2.11, R2.2
unnamed: Q2.3 (D), R5.1
unnamed: C1.1, U3.6 (NRST)
unnamed: R1.1, U3.8 (PA1)
unnamed: R3.1, U3.12 (PA5)
unnamed: R4.1, U3.13 (PA6)
unnamed: R2.1, U3.14 (PA7)
PS: J1.5, J2.5, R1.2
RESET: J3.3, U3.15 (PB0/PB1/PB2/PA8)
SCLK: J1.7, J2.7, R3.2
SWDCLK: J4.4, U3.19 (PA14/PA15)
SWDIO: J4.3, U3.18 (PA13)
S_MISO: U3.10 (PA3)
S_MOSI: J3.2, U3.11 (PA4)
S_SCK: J3.6, U3.1 (PB7/PB8)
TE: J3.4, U3.7 (PA0)
VDD: C2.1, C9.1, J3.17, J3.22, R7.2, U2.5 (OUT), U3.4 (VDD)
